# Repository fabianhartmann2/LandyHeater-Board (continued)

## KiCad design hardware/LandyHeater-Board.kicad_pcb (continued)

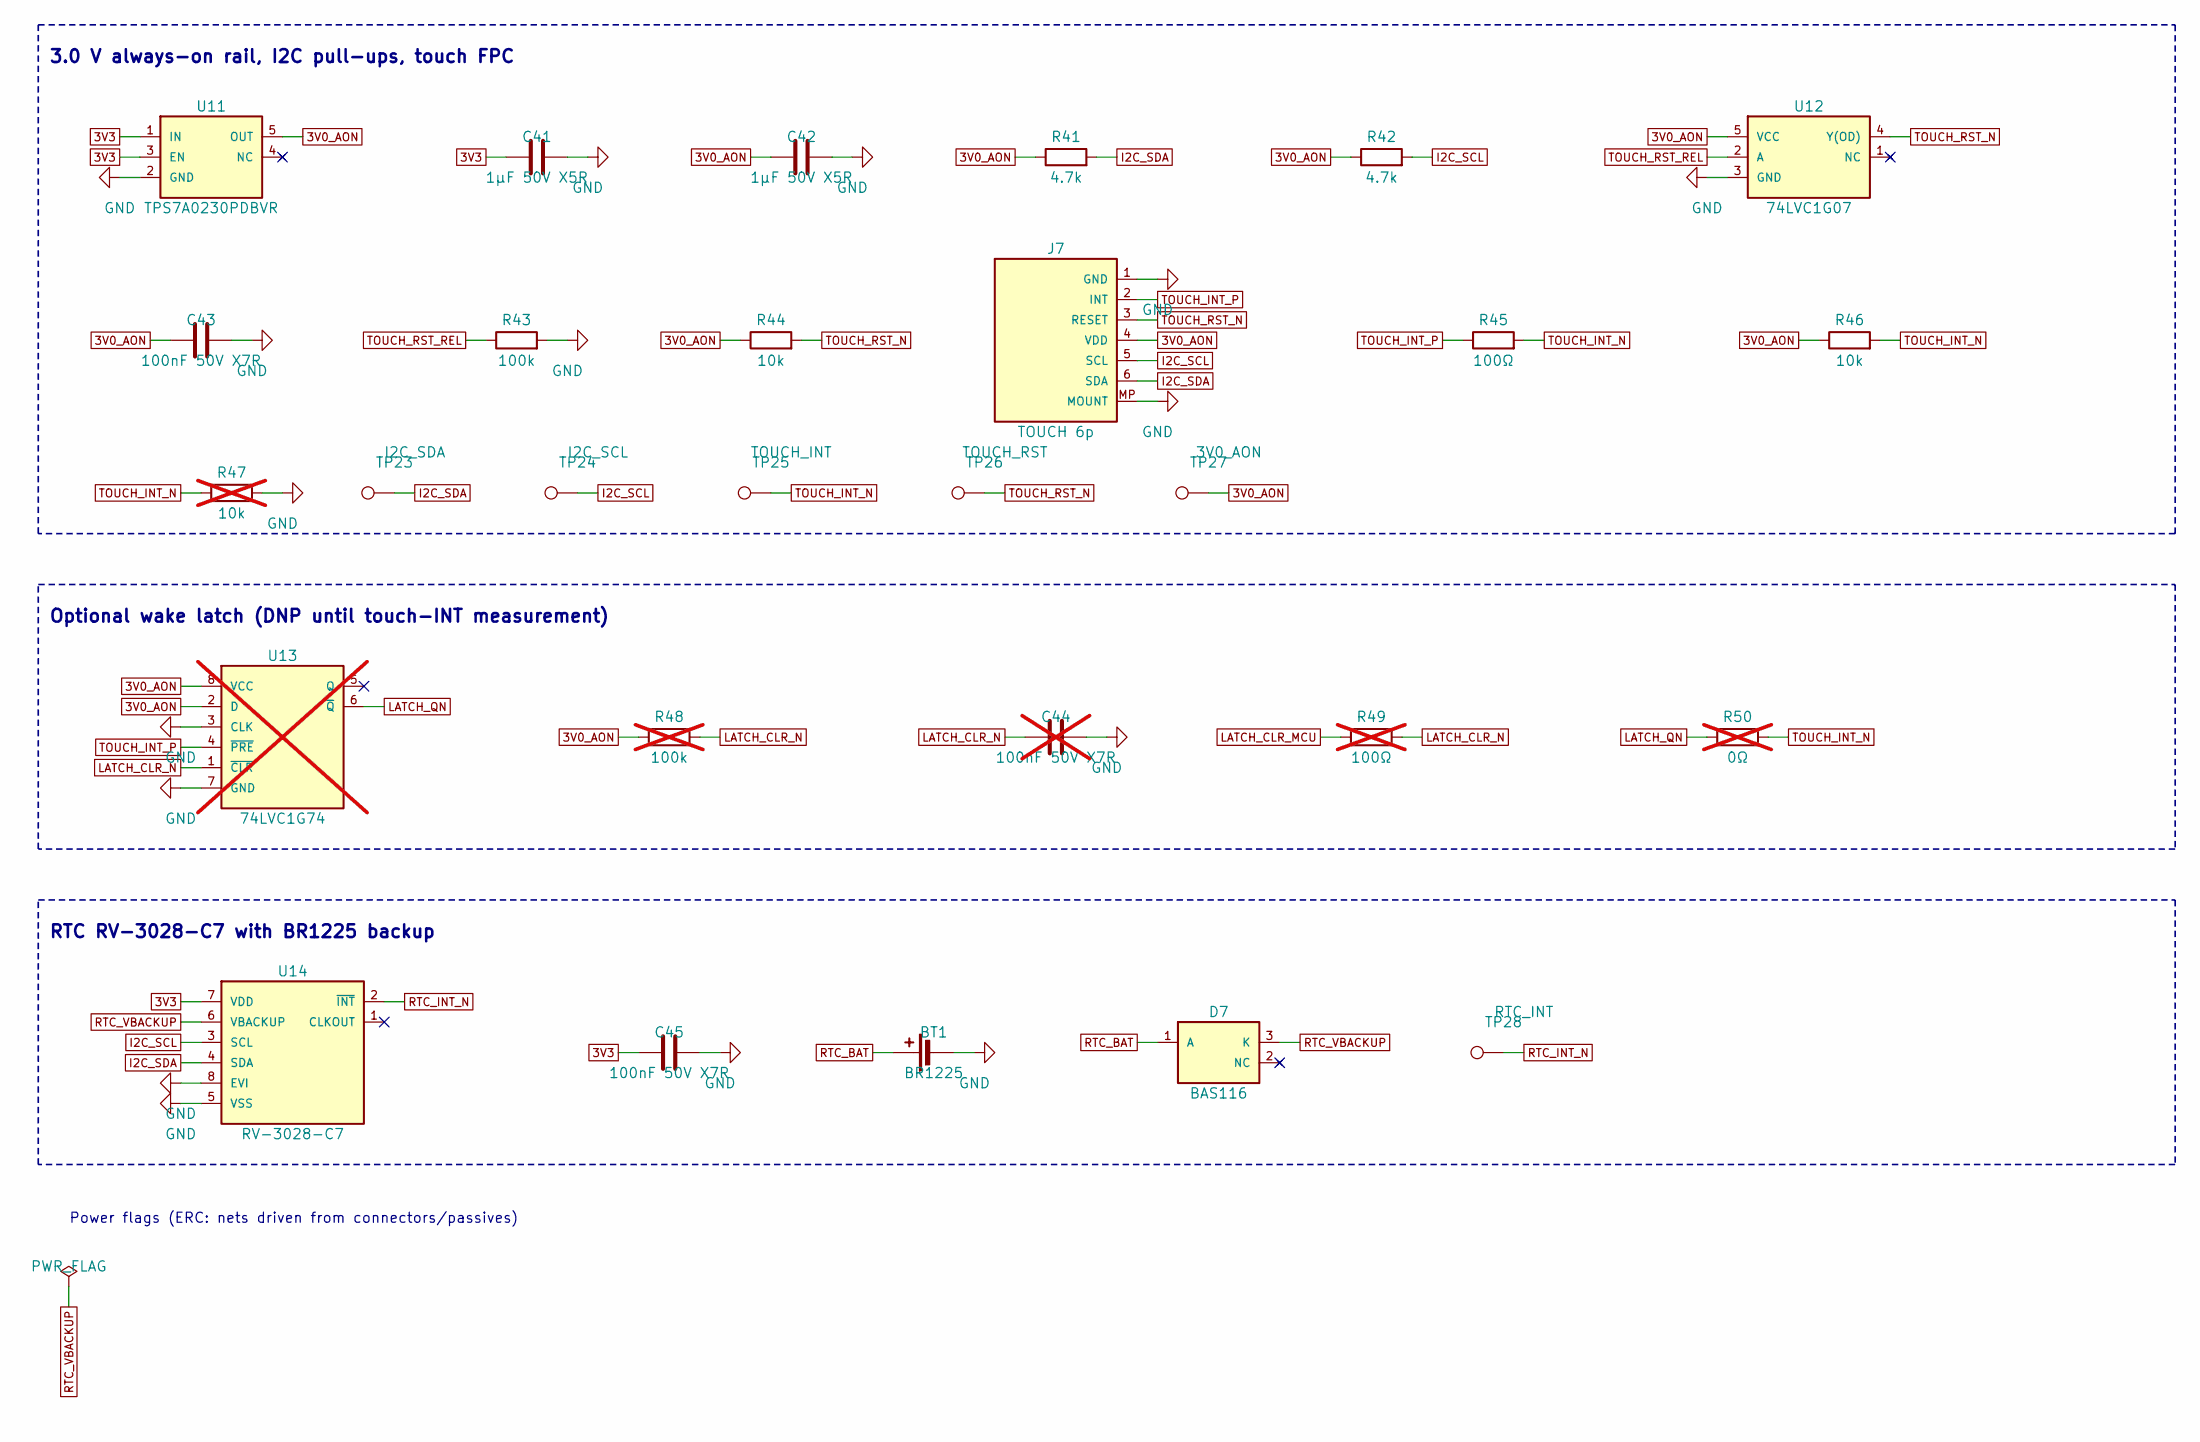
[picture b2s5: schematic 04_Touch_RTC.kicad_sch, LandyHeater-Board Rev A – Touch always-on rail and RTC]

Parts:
BT1: BR1225; BatteryHolder_LINX_BAT-HLD-012-SMT; MPN BAT-HLD-012-SMT; LCSC C5189234
C41, C42: 1µF 50V X5R; C_0603_1608Metric; MPN CL10A105KB8NNNC; LCSC C15849
C43, C45: 100nF 50V X7R; C_0603_1608Metric; MPN 0603B104K500NT; LCSC C30926
C44: 100nF 50V X7R; C_0603_1608Metric; MPN 0603B104K500NT; LCSC C30926; not fitted
D7: BAS116; SOT-23; MPN BAS116,215; LCSC C48502
J7: TOUCH 6p; Hirose_FH12-6S-0.5SH_1x06-1MP_P0.50mm_Horizontal; MPN FH12-6S-0.5SH(55); LCSC C202118
R41, R42: 4.7k; R_0603_1608Metric; MPN 0603WAF4701T5E; LCSC C23162
R43: 100k; R_0603_1608Metric; MPN RC0603FR-07100KL; LCSC C14675
R44, R46: 10k; R_0603_1608Metric; MPN RC0603FR-0710KL; LCSC C98220
R45: 100Ω; R_0603_1608Metric; MPN 0603WAF1000T5E; LCSC C22775
R47: 10k; R_0603_1608Metric; MPN RC0603FR-0710KL; LCSC C98220; not fitted
R48: 100k; R_0603_1608Metric; MPN RC0603FR-07100KL; LCSC C14675; not fitted
R49: 100Ω; R_0603_1608Metric; MPN 0603WAF1000T5E; LCSC C22775; not fitted
R50: 0Ω; R_0603_1608Metric; MPN 0603WAF0000T5E; LCSC C21189; not fitted
TP23: I2C_SDA; TestPoint_Pad_D1.0mm
TP24: I2C_SCL; TestPoint_Pad_D1.0mm
TP25: TOUCH_INT; TestPoint_Pad_D1.0mm
TP26: TOUCH_RST; TestPoint_Pad_D1.0mm
TP27: 3V0_AON; TestPoint_Pad_D1.0mm
TP28: RTC_INT; TestPoint_Pad_D1.0mm
U11: TPS7A0230PDBVR; SOT-23-5; MPN TPS7A0230PDBVR; LCSC C3747031
U12: 74LVC1G07; SOT-23-5; MPN SN74LVC1G07DBVR; LCSC C7394020
U13: 74LVC1G74; VSSOP-8_2.3x2mm_P0.5mm; MPN SN74LVC1G74DCUR; LCSC C70285; not fitted
U14: RV-3028-C7; MicroCrystal_RV-3028-C7; MPN RV-3028-C7-32.768kHz-1ppm-TA-QC; LCSC C3019759

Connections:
3V0_AON: C42.1, C43.1, J7.4 (VDD), R41.1, R42.1, R44.1, R46.1, R48.1, TP27.1, U11.5 (OUT), U12.5 (VCC), U13.2 (D), U13.8 (VCC)
3V3: C41.1, C45.1, U11.1 (IN), U11.3 (EN), U14.7 (VDD); also elsewhere on the board
GND: BT1.2 (-), C41.2, C42.2, C43.2, C44.2, C45.2, J7.1 (GND), J7.MP (MOUNT), R43.2, R47.2, U11.2 (GND), U12.3 (GND), U13.3 (CLK), U13.7 (GND), U14.5 (VSS), U14.8 (EVI); also elsewhere on the board
I2C_SCL: J7.5 (SCL), R42.2, TP24.1, U14.3 (SCL); also elsewhere on the board
I2C_SDA: J7.6 (SDA), R41.2, TP23.1, U14.4 (SDA); also elsewhere on the board
LATCH_CLR_MCU: R49.1; also elsewhere on the board
LATCH_CLR_N: C44.1, R48.2, R49.2, U13.1 (~CLR)
LATCH_QN: R50.1, U13.6 (~Q)
RTC_BAT: BT1.1 (+), D7.1 (A)
RTC_INT_N: TP28.1, U14.2 (~INT)
RTC_VBACKUP: D7.3 (K), U14.6 (VBACKUP)
TOUCH_INT_N: R45.2, R46.2, R47.1, R50.2, TP25.1; also elsewhere on the board
TOUCH_INT_P: J7.2 (INT), R45.1, U13.4 (~PRE)
TOUCH_RST_N: J7.3 (RESET), R44.2, TP26.1, U12.4 (Y(OD))
TOUCH_RST_REL: R43.1, U12.2 (A); also elsewhere on the board

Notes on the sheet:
3.0 V always-on rail, I2C pull-ups, touch FPC
Optional wake latch (DNP until touch-INT measurement)
RTC RV-3028-C7 with BR1225 backup
Power flags (ERC: nets driven from connectors/passives)

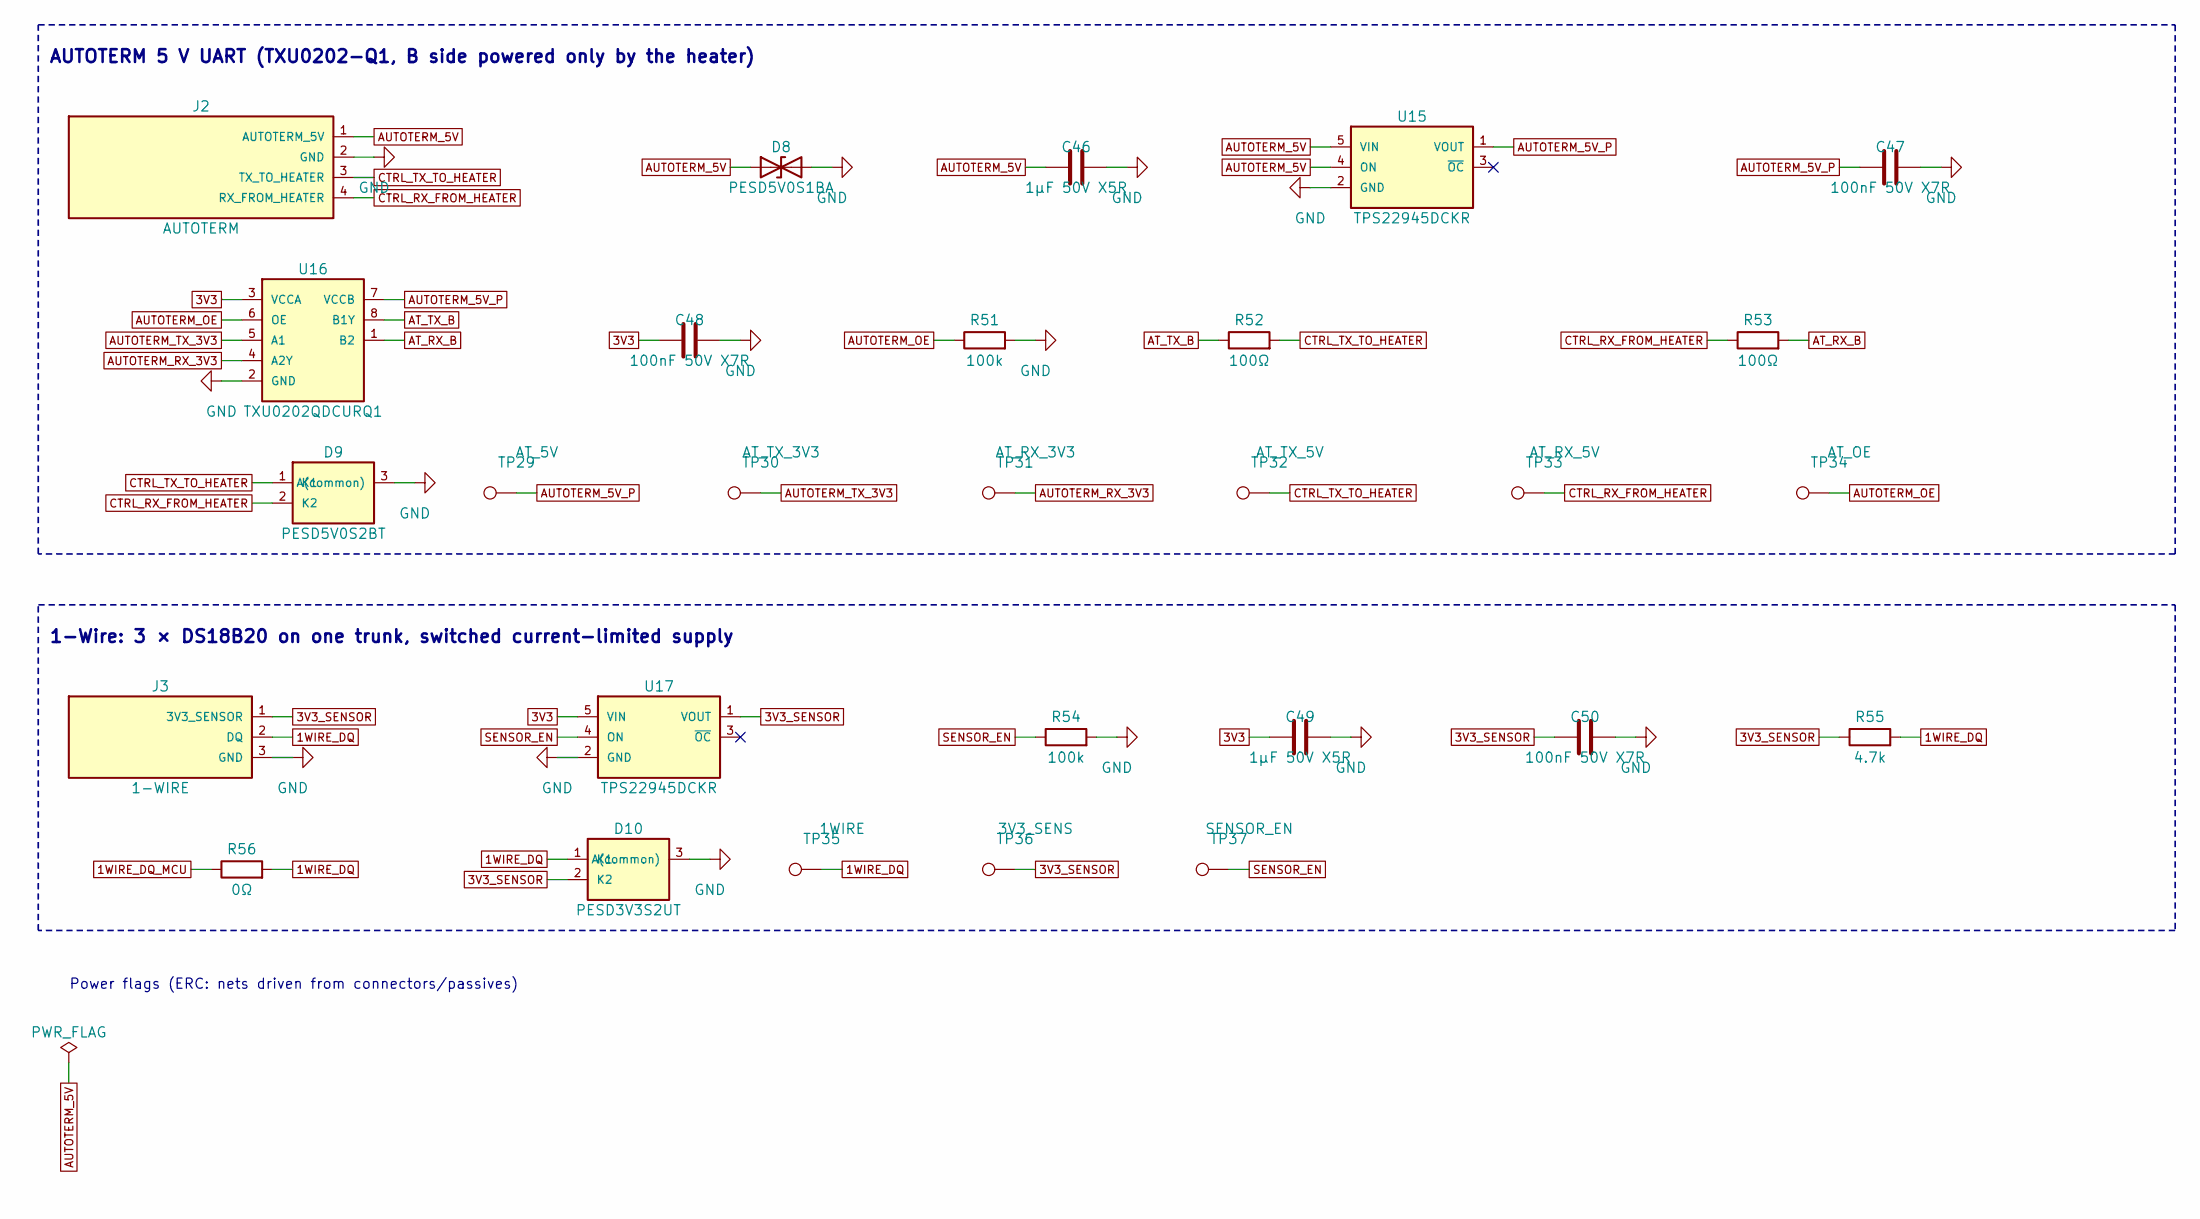
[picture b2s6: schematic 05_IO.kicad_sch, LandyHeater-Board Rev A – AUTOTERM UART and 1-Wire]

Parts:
C46, C49: 1µF 50V X5R; C_0603_1608Metric; MPN CL10A105KB8NNNC; LCSC C15849
C47, C48, C50: 100nF 50V X7R; C_0603_1608Metric; MPN 0603B104K500NT; LCSC C30926
D8: PESD5V0S1BA; D_SOD-323; MPN PESD5V0S1BA,115; LCSC C19224
D9: PESD5V0S2BT; SOT-23; MPN PESD5V0S2BT,215; LCSC C49338
D10: PESD3V3S2UT; SOT-23; MPN PESD3V3S2UT-QR; LCSC C7508770
J2: AUTOTERM; Molex_Nano-Fit_105313-xx04_1x04_P2.50mm_Horizontal; MPN 1053131304; LCSC C17554326
J3: 1-WIRE; Molex_Nano-Fit_105313-xx03_1x03_P2.50mm_Horizontal; MPN 1053131303; LCSC C17198650
R51, R54: 100k; R_0603_1608Metric; MPN RC0603FR-07100KL; LCSC C14675
R52, R53: 100Ω; R_0603_1608Metric; MPN 0603WAF1000T5E; LCSC C22775
R55: 4.7k; R_0603_1608Metric; MPN 0603WAF4701T5E; LCSC C23162
R56: 0Ω; R_0603_1608Metric; MPN 0603WAF0000T5E; LCSC C21189
TP29: AT_5V; TestPoint_Pad_D1.0mm
TP30: AT_TX_3V3; TestPoint_Pad_D1.0mm
TP31: AT_RX_3V3; TestPoint_Pad_D1.0mm
TP32: AT_TX_5V; TestPoint_Pad_D1.0mm
TP33: AT_RX_5V; TestPoint_Pad_D1.0mm
TP34: AT_OE; TestPoint_Pad_D1.0mm
TP35: 1WIRE; TestPoint_Pad_D1.0mm
TP36: 3V3_SENS; TestPoint_Pad_D1.0mm
TP37: SENSOR_EN; TestPoint_Pad_D1.0mm
U15, U17: TPS22945DCKR; SOT-353_SC-70-5; MPN TPS22945DCKR; LCSC C47507
U16: TXU0202QDCURQ1; VSSOP-8_2.3x2mm_P0.5mm; MPN TXU0202QDCURQ1; LCSC C7372013

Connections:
1WIRE_DQ: D10.1 (K1), J3.2 (DQ), R55.2, R56.2, TP35.1
1WIRE_DQ_MCU: R56.1; also elsewhere on the board
3V3: C48.1, C49.1, U16.3 (VCCA), U17.5 (VIN); also elsewhere on the board
3V3_SENSOR: C50.1, D10.2 (K2), J3.1 (3V3_SENSOR), R55.1, TP36.1, U17.1 (VOUT)
AT_RX_B: R53.2, U16.1 (B2)
AT_TX_B: R52.1, U16.8 (B1Y)
AUTOTERM_5V: C46.1, D8.1 (A1), J2.1 (AUTOTERM_5V), U15.4 (ON), U15.5 (VIN); also elsewhere on the board
AUTOTERM_5V_P: C47.1, TP29.1, U15.1 (VOUT), U16.7 (VCCB)
AUTOTERM_OE: R51.1, TP34.1, U16.6 (OE); also elsewhere on the board
AUTOTERM_RX_3V3: TP31.1, U16.4 (A2Y); also elsewhere on the board
AUTOTERM_TX_3V3: TP30.1, U16.5 (A1); also elsewhere on the board
CTRL_RX_FROM_HEATER: D9.2 (K2), J2.4 (RX_FROM_HEATER), R53.1, TP33.1
CTRL_TX_TO_HEATER: D9.1 (K1), J2.3 (TX_TO_HEATER), R52.2, TP32.1
GND: C46.2, C47.2, C48.2, C49.2, C50.2, D8.2 (A2), D9.3 (A(common)), D10.3 (A(common)), J2.2 (GND), J3.3 (GND), R51.2, R54.2, U15.2 (GND), U16.2 (GND), U17.2 (GND); also elsewhere on the board
SENSOR_EN: R54.1, TP37.1, U17.4 (ON); also elsewhere on the board

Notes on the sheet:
AUTOTERM 5 V UART (TXU0202-Q1, B side powered only by the heater)
1-Wire: 3 × DS18B20 on one trunk, switched current-limited supply
Power flags (ERC: nets driven from connectors/passives)

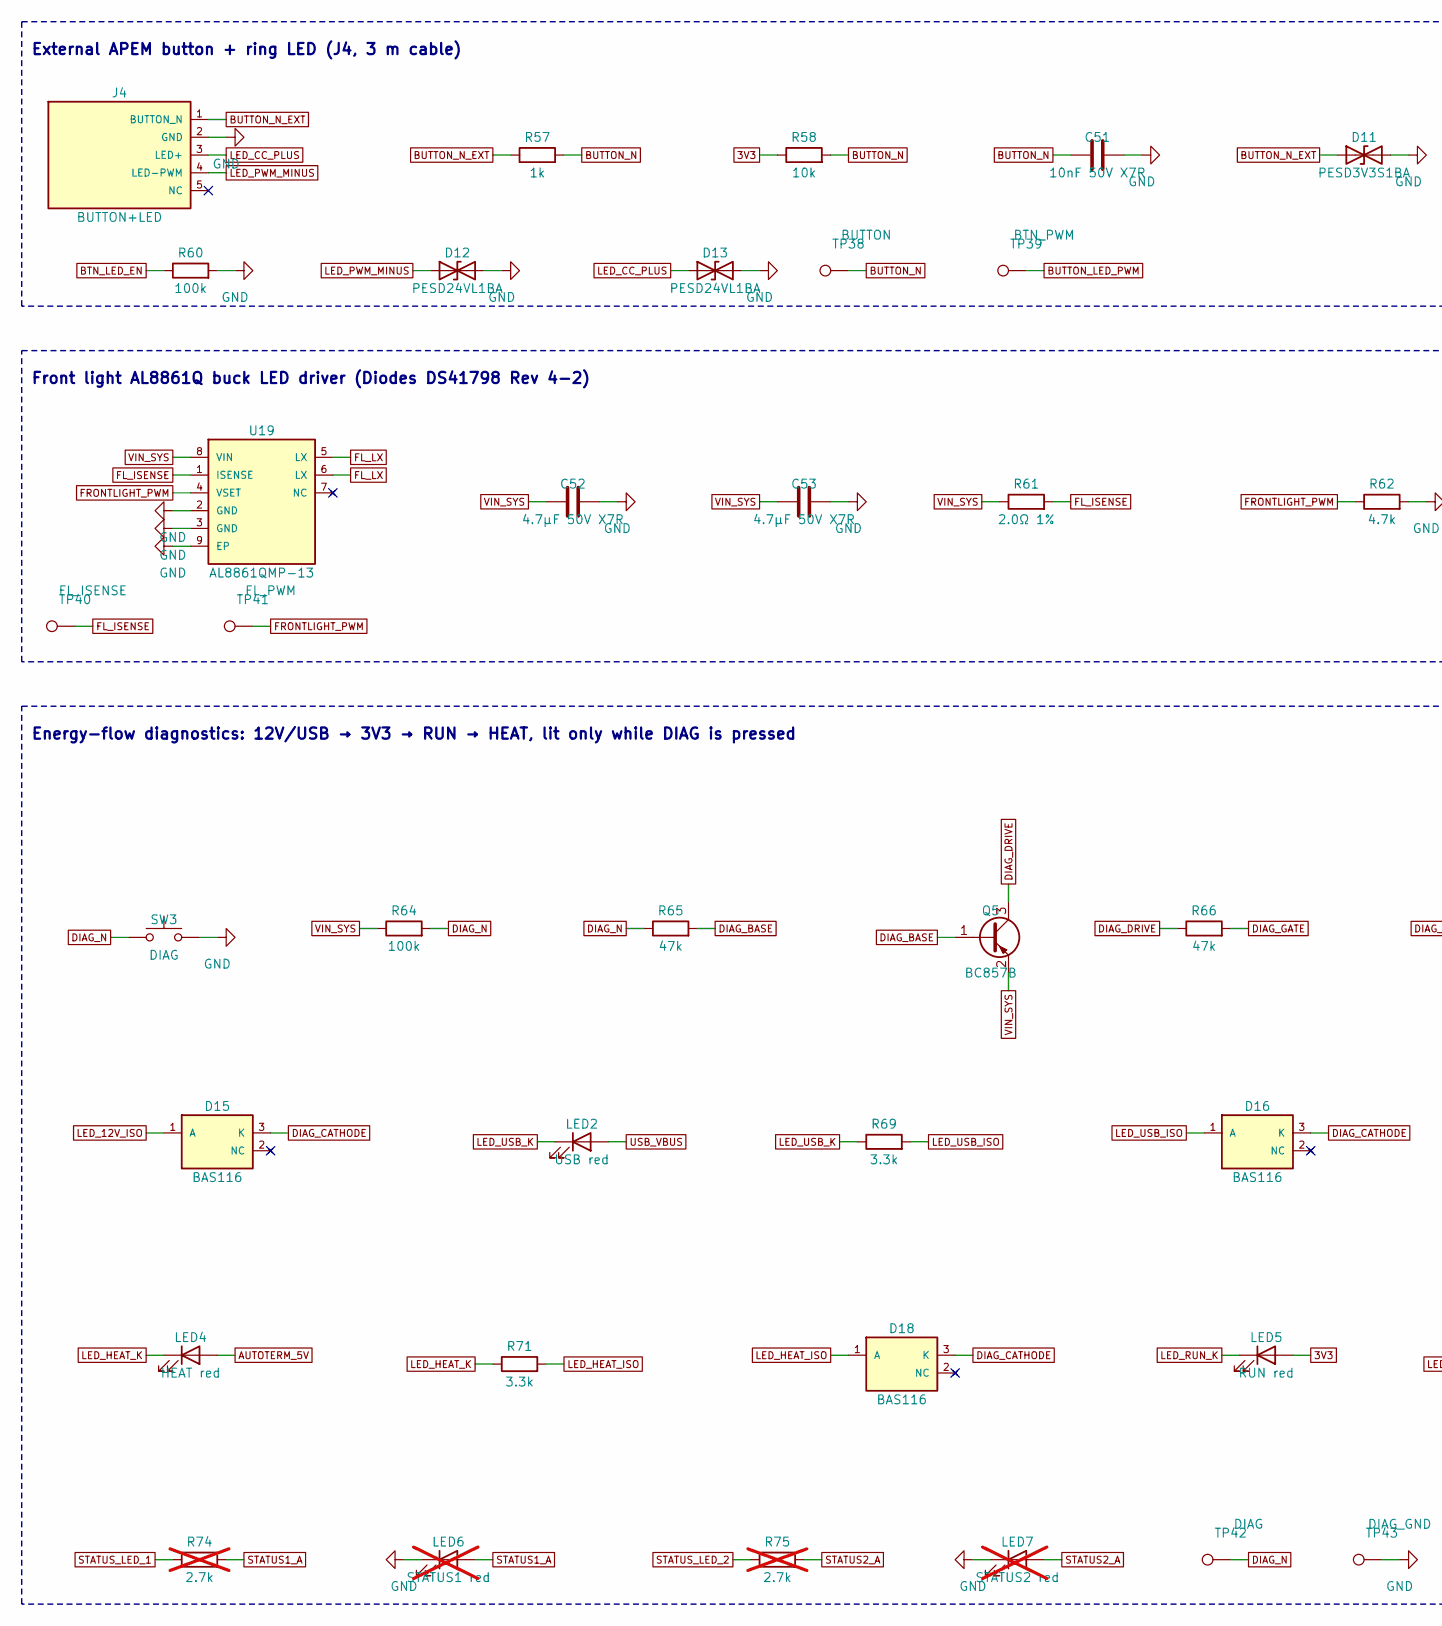
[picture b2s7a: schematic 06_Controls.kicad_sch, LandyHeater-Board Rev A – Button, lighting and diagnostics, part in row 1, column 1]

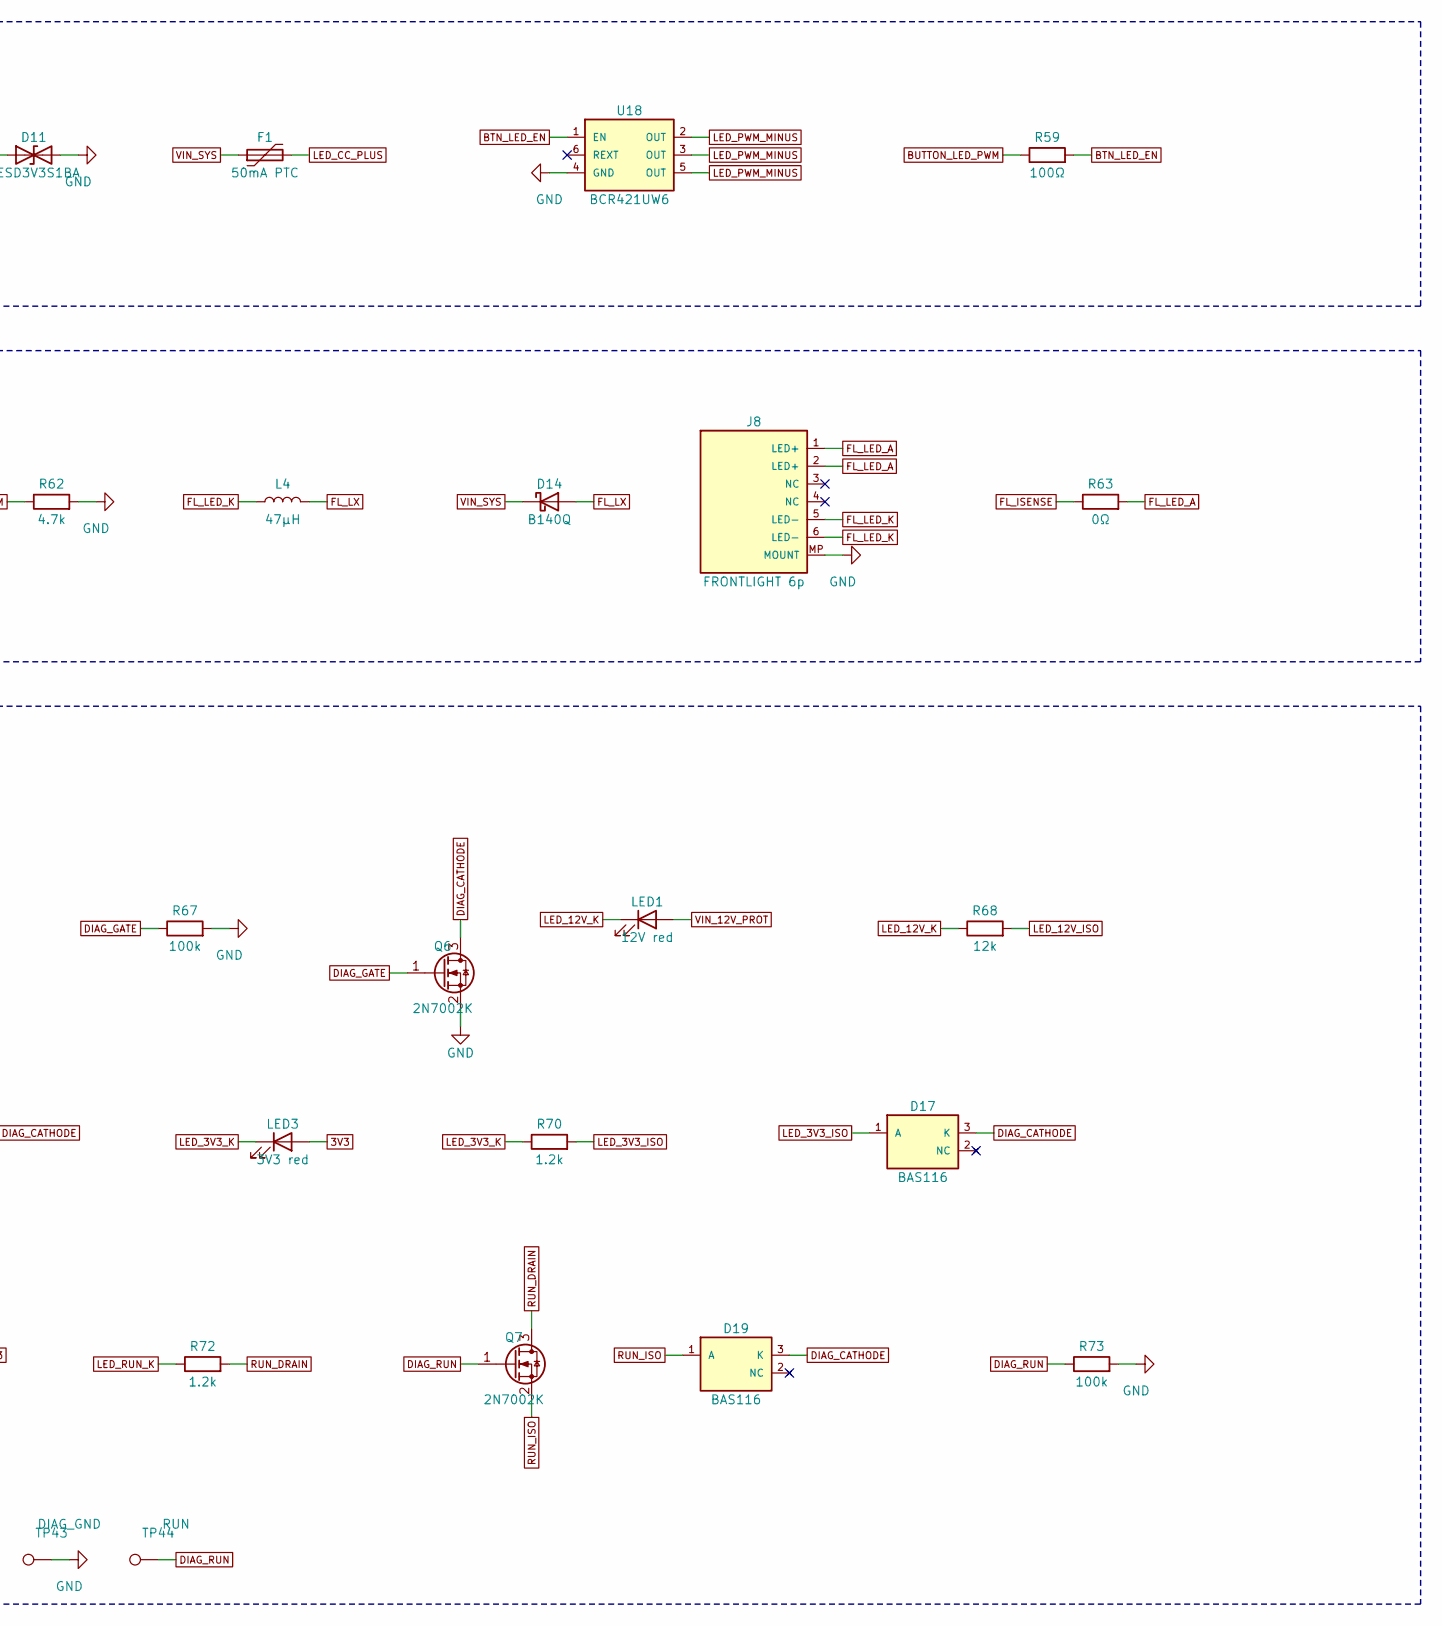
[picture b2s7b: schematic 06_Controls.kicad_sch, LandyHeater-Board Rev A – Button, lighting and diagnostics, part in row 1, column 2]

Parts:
C51: 10nF 50V X7R; C_0603_1608Metric; MPN 0603B103K500NT; LCSC C57112
C52: 4.7µF 50V X7R; C_1210_3225Metric; MPN GCJ32ER71H475KA12L; LCSC C417122
C53: 4.7µF 50V X7R; C_1206_3216Metric; MPN CL31B475KBHNNNE; LCSC C51205
D11: PESD3V3S1BA; D_SOD-323; MPN PESD3V3S1BA; LCSC C7472904
D12, D13: PESD24VL1BA; D_SOD-323; MPN PESD24VL1BA,115; LCSC C69324
D14: B140Q; D_SMA; MPN B140Q-13-F; LCSC C134430
D15, D16, D17, D18, D19: BAS116; SOT-23; MPN BAS116,215; LCSC C48502
F1: 50mA PTC; Fuse_1210_3225Metric; MPN MF-USMF005-2; LCSC C118758
J4: BUTTON+LED; Molex_Nano-Fit_105313-xx05_1x05_P2.50mm_Horizontal; MPN 1053131305; LCSC C17316840
J8: FRONTLIGHT 6p; Hirose_FH12-6S-0.5SH_1x06-1MP_P0.50mm_Horizontal; MPN FH12-6S-0.5SH(55); LCSC C202118
L4: 47µH; L_Taiyo-Yuden_NR-40xx; MPN NRS4018T470MDGJV; LCSC C5355142
LED1: 12V red; LED_0603_1608Metric; MPN LTST-C190KRKT; LCSC C94869
LED2: USB red; LED_0603_1608Metric; MPN LTST-C190KRKT; LCSC C94869
LED3: 3V3 red; LED_0603_1608Metric; MPN LTST-C190KRKT; LCSC C94869
LED4: HEAT red; LED_0603_1608Metric; MPN LTST-C190KRKT; LCSC C94869
LED5: RUN red; LED_0603_1608Metric; MPN LTST-C190KRKT; LCSC C94869
LED6: STATUS1 red; LED_0603_1608Metric; MPN LTST-C190KRKT; LCSC C94869; not fitted
LED7: STATUS2 red; LED_0603_1608Metric; MPN LTST-C190KRKT; LCSC C94869; not fitted
Q5: BC857B; SOT-23; MPN BC857BLT1G; LCSC C111644
Q6, Q7: 2N7002K; SOT-23; MPN 2N7002K-7; LCSC C85047
R57: 1k; R_0603_1608Metric; MPN 0603WAF1001T5E; LCSC C21190
R58: 10k; R_0603_1608Metric; MPN RC0603FR-0710KL; LCSC C98220
R59: 100Ω; R_0603_1608Metric; MPN 0603WAF1000T5E; LCSC C22775
R60, R64, R67, R73: 100k; R_0603_1608Metric; MPN RC0603FR-07100KL; LCSC C14675
R61: 2.0Ω 1%; R_1206_3216Metric; MPN 1206W4F200LT5E; LCSC C25335
R62: 4.7k; R_0603_1608Metric; MPN 0603WAF4701T5E; LCSC C23162
R63: 0Ω; R_0603_1608Metric; MPN 0603WAF0000T5E; LCSC C21189
R65, R66: 47k; R_0603_1608Metric; MPN RC0603FR-0747KL; LCSC C105579
R68: 12k; R_0603_1608Metric; MPN 0603WAF1202T5E; LCSC C22790
R69, R71: 3.3k; R_0603_1608Metric; MPN 0603WAF3301T5E; LCSC C22978
R70, R72: 1.2k; R_0603_1608Metric; MPN 0603WAF1201T5E; LCSC C22765
R74, R75: 2.7k; R_0603_1608Metric; MPN 0603WAF2701T5E; LCSC C13167; not fitted
SW3: DIAG; SW_Push_1P1T_XKB_TS-1187A; MPN TS-1187A-B-A-B; LCSC C318884
TP38: BUTTON; TestPoint_Pad_D1.0mm
TP39: BTN_PWM; TestPoint_Pad_D1.0mm
TP40: FL_ISENSE; TestPoint_Pad_D1.0mm
TP41: FL_PWM; TestPoint_Pad_D1.0mm
TP42: DIAG; TestPoint_Pad_D1.0mm
TP43: DIAG_GND; TestPoint_Pad_D1.0mm
TP44: RUN; TestPoint_Pad_D1.0mm
U18: BCR421UW6; SOT-23-6; MPN BCR421UW6-7; LCSC C194382
U19: AL8861QMP-13; MSOP-8-1EP_3x3mm_P0.65mm_EP1.68x1.88mm; MPN AL8861QMP-13; LCSC C2678638

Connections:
3V3: LED3.2 (A), LED5.2 (A), R58.1; also elsewhere on the board
AUTOTERM_5V: LED4.2 (A); also elsewhere on the board
BTN_LED_EN: R59.2, R60.1, U18.1 (EN)
BUTTON_LED_PWM: R59.1, TP39.1; also elsewhere on the board
BUTTON_N: C51.1, R57.2, R58.2, TP38.1; also elsewhere on the board
BUTTON_N_EXT: D11.1 (A1), J4.1 (BUTTON_N), R57.1
DIAG_BASE: Q5.1 (B), R65.2
DIAG_CATHODE: D15.3 (K), D16.3 (K), D17.3 (K), D18.3 (K), D19.3 (K), Q6.3 (D)
DIAG_DRIVE: Q5.3 (C), R66.1
DIAG_GATE: Q6.1 (G), R66.2, R67.1
DIAG_N: R64.2, R65.1, SW3.1, TP42.1
DIAG_RUN: Q7.1 (G), R73.1, TP44.1; also elsewhere on the board
FL_ISENSE: R61.2, R63.1, TP40.1, U19.1 (ISENSE)
FL_LED_A: J8.1 (LED+), J8.2 (LED+), R63.2
FL_LED_K: J8.5 (LED-), J8.6 (LED-), L4.1
FL_LX: D14.2 (A), L4.2, U19.5 (LX), U19.6 (LX)
FRONTLIGHT_PWM: R62.1, TP41.1, U19.4 (VSET); also elsewhere on the board
GND: C51.2, C52.2, C53.2, D11.2 (A2), D12.2 (A2), D13.2 (A2), J4.2 (GND), J8.MP (MOUNT), LED6.1 (K), LED7.1 (K), Q6.2 (S), R60.2, R62.2, R67.2, R73.2, SW3.2, TP43.1, U18.4 (GND), U19.2 (GND), U19.3 (GND), U19.9 (EP); also elsewhere on the board
LED_3V3_ISO: D17.1 (A), R70.2
LED_3V3_K: LED3.1 (K), R70.1
LED_12V_ISO: D15.1 (A), R68.2
LED_12V_K: LED1.1 (K), R68.1
LED_CC_PLUS: D13.1 (A1), F1.2, J4.3 (LED+)
LED_HEAT_ISO: D18.1 (A), R71.2
LED_HEAT_K: LED4.1 (K), R71.1
LED_PWM_MINUS: D12.1 (A1), J4.4 (LED-PWM), U18.2 (OUT), U18.3 (OUT), U18.5 (OUT)
LED_RUN_K: LED5.1 (K), R72.1
LED_USB_ISO: D16.1 (A), R69.2
LED_USB_K: LED2.1 (K), R69.1
RUN_DRAIN: Q7.3 (D), R72.2
RUN_ISO: D19.1 (A), Q7.2 (S)
STATUS1_A: LED6.2 (A), R74.2
STATUS2_A: LED7.2 (A), R75.2
STATUS_LED_1: R74.1; also elsewhere on the board
STATUS_LED_2: R75.1; also elsewhere on the board
USB_VBUS: LED2.2 (A); also elsewhere on the board
VIN_12V_PROT: LED1.2 (A); also elsewhere on the board
VIN_SYS: C52.1, C53.1, D14.1 (K), F1.1, Q5.2 (E), R61.1, R64.1, U19.8 (VIN); also elsewhere on the board

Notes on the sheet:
External APEM button + ring LED (J4, 3 m cable)
Front light AL8861Q buck LED driver (Diodes DS41798 Rev 4-2)
Energy-flow diagnostics: 12V/USB → 3V3 → RUN → HEAT, lit only while DIAG is pressed

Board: 4 copper layers, 246 parts (87 on the bottom side), 132 nets, no tracks yet.

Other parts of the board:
H1, H2, H3, H4: M2.5; MountingHole_2.7mm_M2.5_Pad_Via

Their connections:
GND: H1.1, H2.1, H3.1, H4.1; also elsewhere on the board

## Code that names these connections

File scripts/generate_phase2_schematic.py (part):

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
    esp: list[Part] = [
        Part("U5", "ESP32-S3-WROOM-1U-N16R8", "RF_Module:ESP32-S3-WROOM-1U", [
            ("1", "GND", "GND"), ("2", "3V3", "3V3_CORE"), ("3", "EN", "CHIP_PU"), ("4", "IO4", "1WIRE_DQ_GPIO"),
            ("5", "IO5", "I2C_SDA"), ("6", "IO6", "I2C_SCL"), ("7", "IO7", "TOUCH_RESET_RELEASE"), ("8", "IO15", "SENSOR_EN"),
            ("9", "IO16", "AUTOTERM_TX_3V3"), ("10", "IO17", "AUTOTERM_RX_3V3"), ("11", "IO18", "LATCH_CLR_GPIO_N"), ("12", "IO8", "EPD_BUSY_GPIO"),
            ("13", "IO19/USB_D-", "USB_D_N_ESP"), ("14", "IO20/USB_D+", "USB_D_P_ESP"), ("15", "IO3", None), ("16", "IO46", None),
            ("17", "IO9", "EPD_SCLK_GPIO"), ("18", "IO10", "EPD_SDIO_GPIO"), ("19", "IO11", "EPD_CS_GPIO_N"), ("20", "IO12", "EPD_DC_GPIO"),
            ("21", "IO13", "EPD_RESET_GPIO_N"), ("22", "IO14", "DISPLAY_EN"), ("23", "IO21", "FRONTLIGHT_PWM"), ("24", "IO47", "AUTOTERM_OE"),
            ("25", "IO48", None), ("26", "IO45", None), ("27", "IO0", "BOOT_N"), ("28", "IO35/PSRAM", None),
            ("29", "IO36/PSRAM", None), ("30", "IO37/PSRAM", None), ("31", "IO38", "BUTTON_LED_PWM"), ("32", "IO39", "DIAG_RUN"),
            ("33", "IO40", "USB_HIGH_CURRENT"), ("34", "IO41", "STATUS_LED_1"), ("35", "IO42", "STATUS_LED_2"),
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        passive("C40", "10pF C0G DNP", "USB_D_N_ESP", "GND", C0603, assembly="DNP", dnp=True, note="USB SI tuning only; default DNP"),
        passive("C41", "10pF C0G DNP", "USB_D_P_ESP", "GND", C0603, assembly="DNP", dnp=True, note="USB SI tuning only; default DNP"),
        passive("R16", "499R", "U0TXD_RAW", "U0TXD_TEST", R0603),
        passive("R54", "33R", "EPD_SCLK_GPIO", "EPD_SCLK", R0603),
        passive("R55", "33R", "EPD_SDIO_GPIO", "EPD_SDIO_MOSI", R0603),
        passive("R56", "33R", "EPD_CS_GPIO_N", "EPD_CS_N", R0603),
        passive("R57", "33R", "EPD_DC_GPIO", "EPD_DC", R0603),
        passive("R58", "33R", "EPD_RESET_GPIO_N", "EPD_RESET_N", R0603),
        passive("R59", "33R", "EPD_BUSY", "EPD_BUSY_GPIO", R0603),
        passive("C42", "10pF C0G DNP", "EPD_SCLK", "GND", C0603, assembly="DNP", dnp=True, note="SPI edge-rate tuning; default DNP"),
        passive("C43", "10pF C0G DNP", "EPD_SDIO_MOSI", "GND", C0603, assembly="DNP", dnp=True),
        passive("C44", "10pF C0G DNP", "EPD_CS_N", "GND", C0603, assembly="DNP", dnp=True),
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        passive("R31", "100k DNP", "3V0_TOUCH_AON", "LATCH_CLR_N", R0603, assembly="DNP", dnp=True),
        passive("C39", "100nF DNP", "LATCH_CLR_N", "GND", C0603, assembly="DNP", dnp=True, note="Power-on clear for optional wake latch"),
        passive("R69", "100R DNP", "LATCH_CLR_GPIO_N", "LATCH_CLR_N", R0603, assembly="DNP", dnp=True, note="Populate only with U13 latch; GPIO18 pulses low after touch INT releases"),
        passive("R70", "0R DNP", "LATCH_Q_N", "TOUCH_INT_N", R0603, assembly="DNP", dnp=True, note="Populate only with U13 latch; remove R28, R29 and R30"),
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        passive("C30", "100nF", "3V3_CORE", "GND", C0603),
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        Part("D10", "B140Q-13-F", "Diode_SMD:D_SMA", [("1", "K", "VIN_SYS"), ("2", "A", "FL_LX")], mpn="B140Q-13-F", manufacturer="Diodes Inc.", datasheet="https://www.diodes.com/assets/Datasheets/ds38236.pdf", note="Automotive 1-A/40-V Schottky; KiCad diode pad 1 is K"),
        passive("R43", "2.0R 1% 0.25W", "VIN_SYS", "FL_ISENSE", "Resistor_SMD:R_1206_3216Metric_Pad1.30x1.75mm_HandSolder"),
        connector("J8", "FH12-6S-0.5SH(55) FRONTLIGHT", "Connector_FFC-FPC:Hirose_FH12-6S-0.5SH_1x06-1MP_P0.50mm_Horizontal", ["FL_LED_A", "FL_LED_A", None, None, "FL_LED_K", "FL_LED_K"], mpn="FH12-6S-0.5SH(55)", manufacturer="Hirose", note="PROVISIONAL pin/contact orientation; verify display"),
        passive("R44", "0R", "FL_ISENSE", "FL_LED_A", R0603),
        connector("TP20", "FRONTLIGHT_CURRENT", "TestPoint:TestPoint_Pad_D1.0mm", ["FL_ISENSE"], assembly="DNP", dnp=True),
        Part("SW3", "DIAG KMR221GLFS", "Button_Switch_SMD:SW_Push_1P1T_NO_CK_KMR2", [("1", "A", "DIAG_N"), ("2", "B", "GND")], mpn="KMR221GLFS", manufacturer="C&K"),
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
    by_ref = {part.ref: part for part in all_parts}
    expected_esp = {
        "4": "1WIRE_DQ_GPIO", "5": "I2C_SDA", "6": "I2C_SCL", "7": "TOUCH_RESET_RELEASE",
        "8": "SENSOR_EN", "9": "AUTOTERM_TX_3V3", "10": "AUTOTERM_RX_3V3", "11": "LATCH_CLR_GPIO_N",
        "12": "EPD_BUSY_GPIO", "13": "USB_D_N_ESP", "14": "USB_D_P_ESP",
        "17": "EPD_SCLK_GPIO", "18": "EPD_SDIO_GPIO", "19": "EPD_CS_GPIO_N",
        "20": "EPD_DC_GPIO", "21": "EPD_RESET_GPIO_N", "22": "DISPLAY_EN",
        "23": "FRONTLIGHT_PWM", "24": "AUTOTERM_OE", "27": "BOOT_N",
        "31": "BUTTON_LED_PWM", "32": "DIAG_RUN", "33": "USB_HIGH_CURRENT",
        "34": "STATUS_LED_1", "35": "STATUS_LED_2", "38": "TOUCH_INT_N", "39": "BUTTON_N",
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    if c37_nets != {"EPD_PREVGL", "GND"}:
        raise ValueError("C37 must connect EPD_PREVGL to GND per the display reference circuit")

    if {net for _number, _name, net in by_ref["R5"].pins} != {"USB_VBUS", "USB_CURRENT_OUT1"}:
        raise ValueError("TUSB321 OUT1 pull-up must return to USB_VBUS")
    if {net for _number, _name, net in by_ref["Q8"].pins} != {"USB_CURRENT_OUT1", "GND", "USB_HIGH_CURRENT"}:
        raise ValueError("Q8 USB-current-domain isolator wiring mismatch")

    expected_esd_arrays = {
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            raise ValueError(f"Common-anode ESD-array pinout mismatch on {ref}: {actual}")

    u18 = {number: net for number, _name, net in by_ref["U18"].pins}
    if u18.get("1") != "BUTTON_LED_EN" or any(u18.get(pin) != "LED_PWM_MINUS" for pin in ("2", "3", "5")):
        raise ValueError("BCR421 native PWM/output topology mismatch")

    for ref in ("C40", "C41", "C42", "C43", "C44", "C45", "C46"):
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                    "GND", "EPD_VDD", None, "EPD_VSH1", "EPD_PREVGH", "EPD_VSL", "EPD_PREVGL", "EPD_VCOM"]
    if [net for _number, _name, net in by_ref["J6"].pins] != expected_epd:
        raise ValueError("J6 E-paper pinout no longer matches GDEY029T94-FT01 Rev. 1.0")
    if [net for _number, _name, net in by_ref["J7"].pins] != ["GND", "TOUCH_INT_PANEL_N", "TOUCH_RESET_N", "3V0_TOUCH_AON", "I2C_SCL", "I2C_SDA"]:
        raise ValueError("J7 touch pinout mismatch")
    if [net for _number, _name, net in by_ref["J8"].pins] != ["FL_LED_A", "FL_LED_A", None, None, "FL_LED_K", "FL_LED_K"]:
        raise ValueError("J8 frontlight pinout mismatch")

    expected_polarity = {
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
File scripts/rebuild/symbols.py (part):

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}

CONN: dict[str, dict] = {
    "J1": dict(pins=["1", "2"], names=["BATT_12V_IN", "GND"]),
    "J2": dict(pins=["1", "2", "3", "4"], names=["AUTOTERM_5V", "GND", "TX_TO_HEATER", "RX_FROM_HEATER"]),
    "J3": dict(pins=["1", "2", "3"], names=["3V3_SENSOR", "DQ", "GND"]),
    "J4": dict(pins=["1", "2", "3", "4", "5"], names=["BUTTON_N", "GND", "LED+", "LED-PWM", "NC"]),
    "USBC": dict(pins=["A4", "A9", "B4", "B9", "A5", "B5", "A6", "B6", "A7", "B7", "A8", "B8", "A1", "A12", "B1", "B12", "SH"],
                 names=["VBUS", "VBUS", "VBUS", "VBUS", "CC1", "CC2", "D+", "D+", "D-", "D-", "SBU1", "SBU2",
                        "GND", "GND", "GND", "GND", "SHIELD"]),
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
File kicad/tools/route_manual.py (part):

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# F) Linke Modul-Pinreihe (Pins 4–12) durch den Engpass vor dem Modul (U5, C16, R12/R13 davor, Status-LED-
#    Spalte R32–R35 neben dem BT1-Lappen). Freerouting findet hier keinen Weg (Probeläufe 13–100 offen).
#    - EN (Pin 3): direkt über C15.1 zu U5.1 (Gasse zwischen C15 und U5, TPS3808: C am Ausgang nah).
#    - STATUS_LED_1 (Pin 4) über L4 zu einem Via rechts von D20, auf L1 über D20 und links an R32/R34 entlang.
#    - DIAG_RUN (Pin 6) auf L1 unter U5 hindurch (Gasse U5/C16) zum Via, Rest per Freerouting auf L4.
#    - STATUS_LED_2 (Pin 5) über L4 zu einem Via rechts der LED-Spalte, auf L1 zwischen R33 und R35 hinein.
#    - SDA/SCL: Pull-ups R12/R13 auf L1 in der Gasse zwischen R12/R13 und der Via-Spalte.
#    - übrige Pins (7, 10–12) und Pin 21: nur Fan-out-Via (x 151,45: 0,75 mm zu den Modulpads), Rest Freerouting.
#    Alle L4-Abschnitte liegen unter der 3V3-Hälfte von L3 (keine Spaltkreuzung, Y-03).
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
